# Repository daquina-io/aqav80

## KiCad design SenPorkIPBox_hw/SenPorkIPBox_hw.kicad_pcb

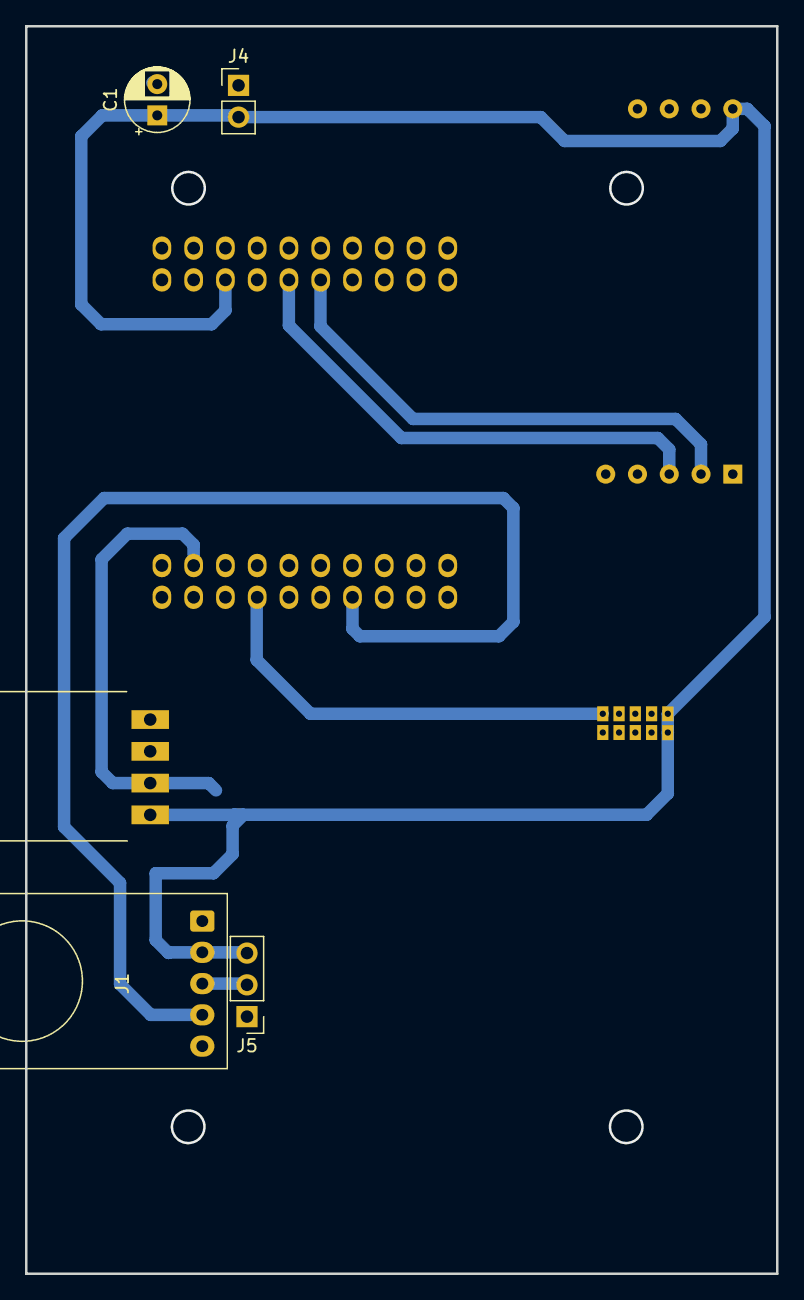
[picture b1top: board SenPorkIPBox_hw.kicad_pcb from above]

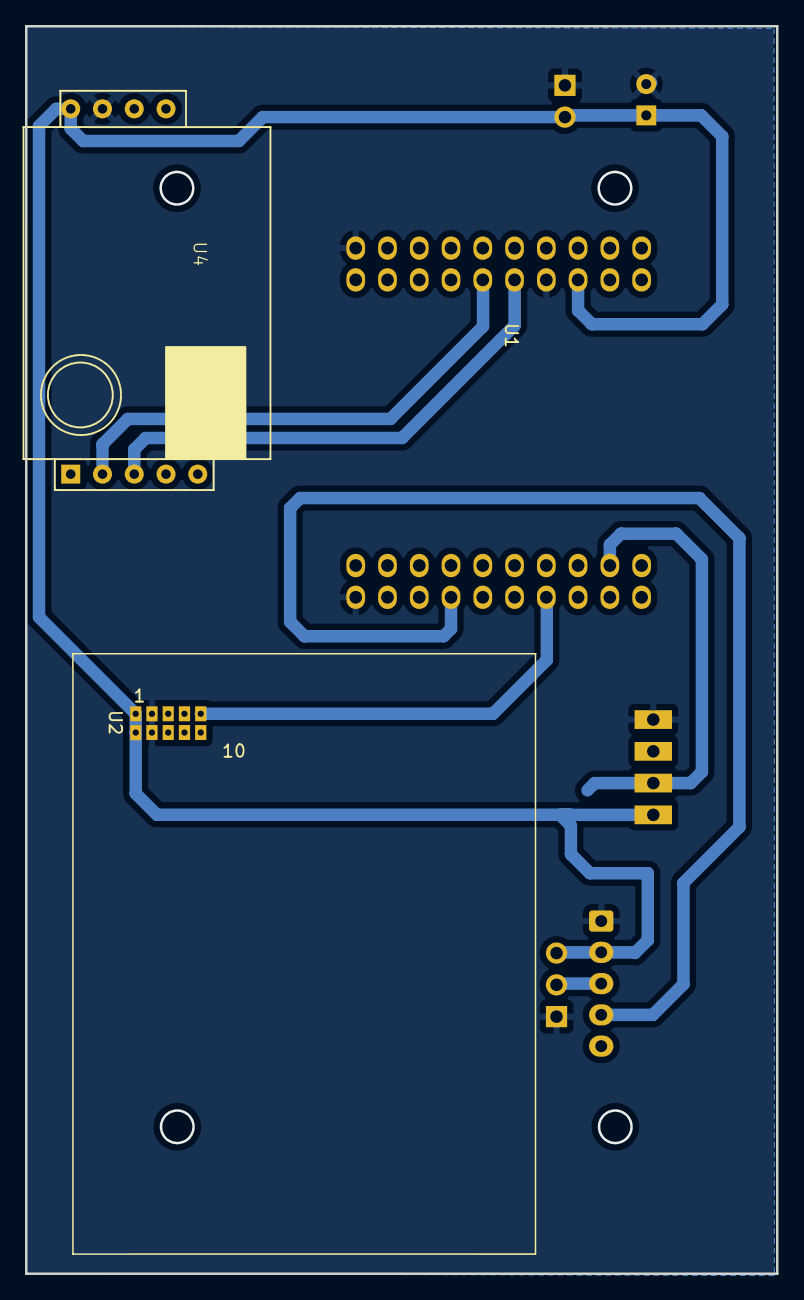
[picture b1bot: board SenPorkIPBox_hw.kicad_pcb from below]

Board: 2 copper layers, 60.0 x 99.8 mm, 8 parts (3 on the bottom side), 8 nets.

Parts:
C1: C_Polarized_US; CP_Radial_D5.0mm_P2.50mm
J1: Mic_max9814_x05_Pin; mic_max9814
J4: Power_input; PinHeader_1x02_P2.54mm_Vertical
J5: MicGain_Jumper; PinHeader_1x03_P2.54mm_Vertical
U1: TTGO-32-MINI; TTGO-32-MINI_NOBORDER
U2: PMS7003
U3: DHT11; DHT11_through_hole
U4: MH-Z19C

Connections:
/GAIN: J1.3, J5.2
/IO13: U1.18 (TCK), U3.2 (IO)
/IO14: U1.13 (TMS), U2.9 (Tx)
/IO16: U1.29 (16), U4.2 (Rxd)
/IO17: U1.31 (17), U4.3 (Txd)
/MIC: J1.4, U1.7 (35)
GND: C1.2, J1.1, J4.1, J5.1, U1.1 (GND), U1.22 (GND), U1.33 (GND), U2.3 (GND), U2.4 (GND), U3.4 (GND), U4.7 (GND)
VCC: C1.1, J1.2, J4.2, J5.3, U1.35 (5V), U2.1 (VCC), U2.2 (VCC), U3.1 (VCC), U4.6 (Vin)

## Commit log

2023-07-23 Change board from esp8266 to esp32, Update libraries versions and make it explicit in the project dependencies
2023-07-25 Add libraries dependencies
2023-07-25 Add base framework of the firmware. Create one task for each sensor reading (Particle matter, Sound level, CO2, Humidity and Temperature). Create one task that took arrays of samples for each variabl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
2023-08-22 Corrige pines Rx=gpio16 y Tx=gpio17 de sensor CO2 que corresponden con SerialHardware-2. Corrige pin Rx=gpio14 de sensor Plantower y se habilita SerialSoftware para estos. Crea estructura json para g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
2023-09-28 Cambios introducidos por uagaviria. Agrega envío de datos mqtt y la librería wifimanager
2023-09-28 Agrega dependencia de wifimanager
2023-09-28 ignora carpeta vscode
2023-09-28 ignorar carpeta vscode
2023-09-28 ignore variables.h
2023-09-28 Agrega carpeta .vscode a archivo .ignore
2023-09-28 Prueba de conexión
2023-10-05 Re estructura carpetas para tener en el mismo proyecto firmware, y configuraciones de infraestructura
2023-10-10 Ajusta la configuracion del parser del mqtt_consumer para procesar el payload de formato json y crear una estructura de datos de acuerdo al esquema recomendado para influxdb. El input es un json con 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
2023-10-10 Ajusta en envio de datos mqtt a el topic tele/{location}/{sensor_id} con el payload {field:[{snd:value},{co2:value},{pm25:value},{hum:value},{temp:value}]} en formato json
2023-12-11 Agrega variables.h al gitignore
2023-12-11 Agrega codigo relacionado con la conexion wifi y la modificacion de @uagaviria a la libreria https://github.com/daquina-io/WiFiManager
2023-12-11 Agrega verificacion de reconexion del cliente mqtt
2024-01-28 Agrega archivo de diseño de la PCB para caja ip https://didacticaselectronicas.com/index.php/cajas-para-proyectos/impermeables/box-imp-blk03-detail
2024-01-28 Agrega proyecto en Flatcam para producir maquinado
2024-03-21 Agrega contenedor de grafana
2024-05-01 Add initial vectorized query functions to get data from sensors
2024-05-25 Reforma la manera de hacer el query, ya es posible agregar filtros por tags, measurements y fields. Agrega filtro general para valores ma'ximos https://docs.influxdata.com/flux/v0/stdlib/universe/fil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
2024-05-27 Change way to load env vars
2024-05-27 Add html report with dygraphs per variable, adjust query construction function to specify the aggregation logic for the tags
2025-01-18 Agrega servicio de proxy con caddy y así generar certificados ssl para cada servicio
2025-01-18 Agrega credenciales de acceso en archivo externo
2025-01-23 Agrega path del binario generado para usar en scripts que firma criptográficamente el archivo
2025-01-23 Agrega al ignore las claves privada y publica para firmar y verificar los binarios del firmware
2025-01-23 Agrega la posibilidad de actualizar remotamente el firmware del dispositivo ante un mensaje mqtt para después de descargar un binario firmado criptográficamente, verificarlo ejecutar el procedimiento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
2025-02-10 Crea capa de abstracción de hardware para manejar los sensores, reemplaza sensor de temperatura dht22 por sht40
2025-02-13 Agrega la posibilidad de tener data mock de la lectura de sensores ficticios
2025-03-02 Agrega multiples tipos de sensor de temperatura
2025-03-02 Separa por clases en diferentes archivos resposabilidades como logging, actualización ota, manejo de la red, manejo de los datos
2025-03-03 Arregla implementación de clase taskmanager que tenía errores al momento de hacer linking debido a la manera que está hecha la librería TaskScheduler
2025-03-04 Agrega clase para organizar los parametros secretos de la aplicación
2025-03-04 Agrega singleton para gestionar la obtención de datos de cada sensor y su posterior usando un scheduler. El singleton permite configurar periodicidad para cada task
2025-03-04 Borra archivos que ya no son necesarios
2025-03-04 Actualiza .gitignore con secrets.h
2025-03-04 Mejora las verificaciones de conectividad para evitar que se caigan los sensores
2025-03-06 Agrega banderas de compilación para optimizar el tamaño del binario
2025-03-06 Mejora implemetación por medio de clases abstractas para tener varios sensores de temperatura
2025-03-06 Mejora la carga del archivo de firmware para hacer la actualización ota
2025-03-20 Agrega funciones para mejorar la disponibilidad en la lectura de los datos del sensor co2 mh-z19
2025-03-20 agrega función para generar id del cliente mqtt
2025-07-13 feat: Add support for senseair s8 co2 sensor
2025-07-15 feat: Add support for dht11 sensor
2025-08-10 Disable reset settings for wifimanager
